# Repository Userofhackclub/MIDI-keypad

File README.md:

# MIDI-keypad
## An electronic instrument based around a Waveshare ESP32-S3-Zero.

Chosen in the Half life project because I personally always wanted an instrument but never had the chance to get one when I was younger so making my own is even better! 

Its intentionally simplistic because I wanted something that anyone can understand at a first glance and also because of budget and time constraints as well.

## Features

- a Waveshare ESP32-S3-Zero, the thing that actually makes everything work
- three buttons typical of a mechanical keyboard
- a rotary encoder
- and two potentiometers
  
## Bill of materials
[bom.md](https://github.com/user-attachments/files/33940341/bom.md)

| Id | Designator | Footprint | Quantity | Designation | Supplier and ref |
|----|------------|-----------|----------|-------------|------------------|
| 1 | D1, D2 | LED_SK6812MINI-E_3.2x2.8mm_P1.5mm_ReverseMount | 2 | SK6812MINI-E | keeb.io (25-pack) |
| 2 | RV1, RV2 | Potentiometer_Bourns_PTA1543_Single_Slide | 2 | R_Potentiometer_MountingPin | Mouser |
| 3 | SW1, SW2, SW3 | Kailh Choc Low-Profile Switches | 3 | SW_Push | Kailh |
| 4 | SW4 | RotaryEncoder_Alps_EC11E-Switch_Vertical_H20mm | 1 | RotaryEncoder_Switch_MP | Adafruit |
| 5 | U1 | Waveshare ESP32-S3-Zero | 1 | Waveshare ESP32-S3-ZERO | Waveshare |

## Its schematic and PCB

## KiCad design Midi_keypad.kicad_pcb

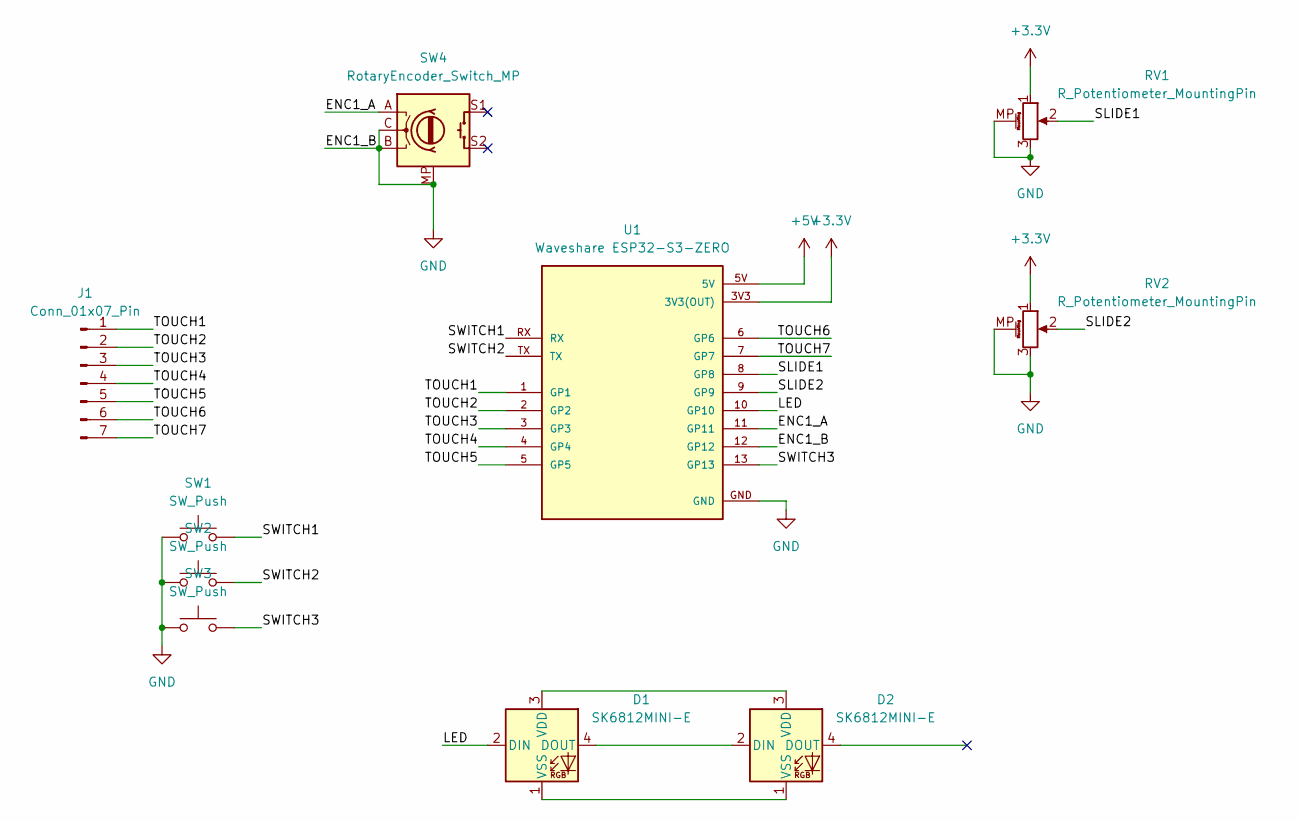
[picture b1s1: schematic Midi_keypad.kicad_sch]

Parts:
D1, D2: SK6812MINI-E; LED_SK6812MINI-E_3.2x2.8mm_P1.5mm_ReverseMount
J1: Conn_01x07_Pin; Capacitive keys
RV1, RV2: R_Potentiometer_MountingPin; Potentiometer_Bourns_PTA1543_Single_Slide
SW1, SW2, SW3: SW_Push; Kailh Choc Low-Profile Switches
SW4: RotaryEncoder_Switch_MP; RotaryEncoder_Alps_EC11E-Switch_Vertical_H20mm
U1: Waveshare ESP32-S3-ZERO; Waveshare ESP32-S3-Zero; PARTREV NA

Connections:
+3.3V: RV1.1, RV2.1, U1.3V3 (3V3(OUT))
+5V: U1.5V
/ENC1_A: SW4.A, U1.11 (GP11)
/LED: D1.2 (DIN), U1.10 (GP10)
/SLIDE1: RV1.2, U1.8 (GP8)
/SLIDE2: RV2.2, U1.9 (GP9)
/SWITCH1: SW1.2, U1.RX
/SWITCH2: SW2.2, U1.TX
/SWITCH3: SW3.2, U1.13 (GP13)
/TOUCH1: J1.1, U1.1 (GP1)
/TOUCH2: J1.2, U1.2 (GP2)
/TOUCH3: J1.3, U1.3 (GP3)
/TOUCH4: J1.4, U1.4 (GP4)
/TOUCH5: J1.5, U1.5 (GP5)
/TOUCH6: J1.6, U1.6 (GP6)
/TOUCH7: J1.7, U1.7 (GP7)
GND: RV1.3, RV1.MP (MountPin), RV2.3, RV2.MP (MountPin), SW1.1, SW2.1, SW3.1, SW4.B, SW4.C, SW4.MP, U1.12 (GP12), U1.GND
unnamed: D1.4 (DOUT), D2.2 (DIN)
unnamed: D1.3 (VDD), D2.3 (VDD)
unnamed: D1.1 (VSS), D2.1 (VSS)

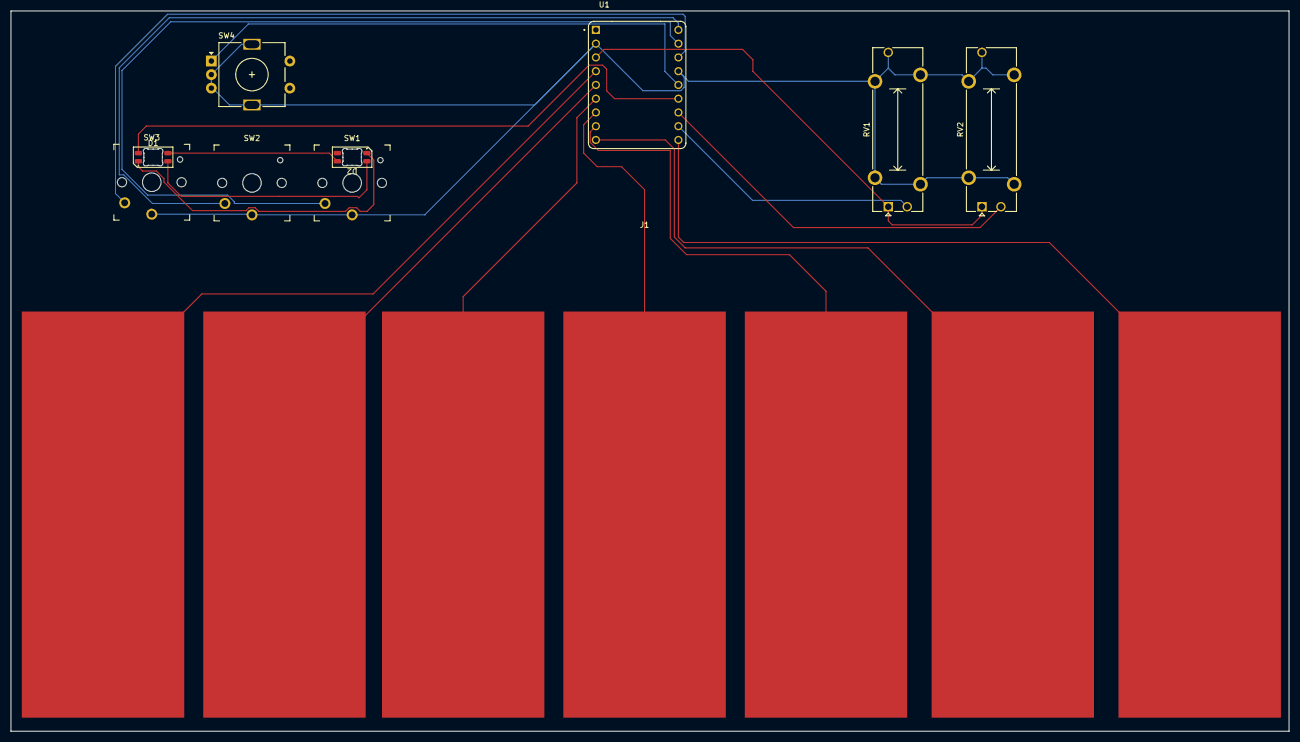
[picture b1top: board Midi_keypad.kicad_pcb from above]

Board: 2 copper layers, 236.0 x 133.0 mm, 10 parts (0 on the bottom side), 19 nets.
